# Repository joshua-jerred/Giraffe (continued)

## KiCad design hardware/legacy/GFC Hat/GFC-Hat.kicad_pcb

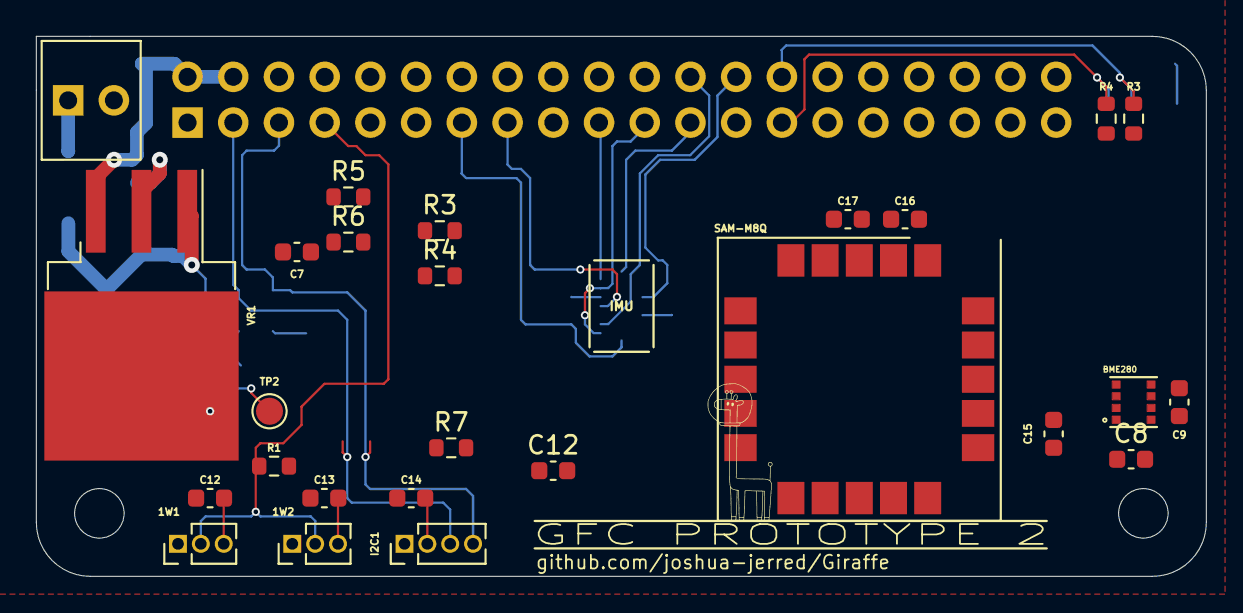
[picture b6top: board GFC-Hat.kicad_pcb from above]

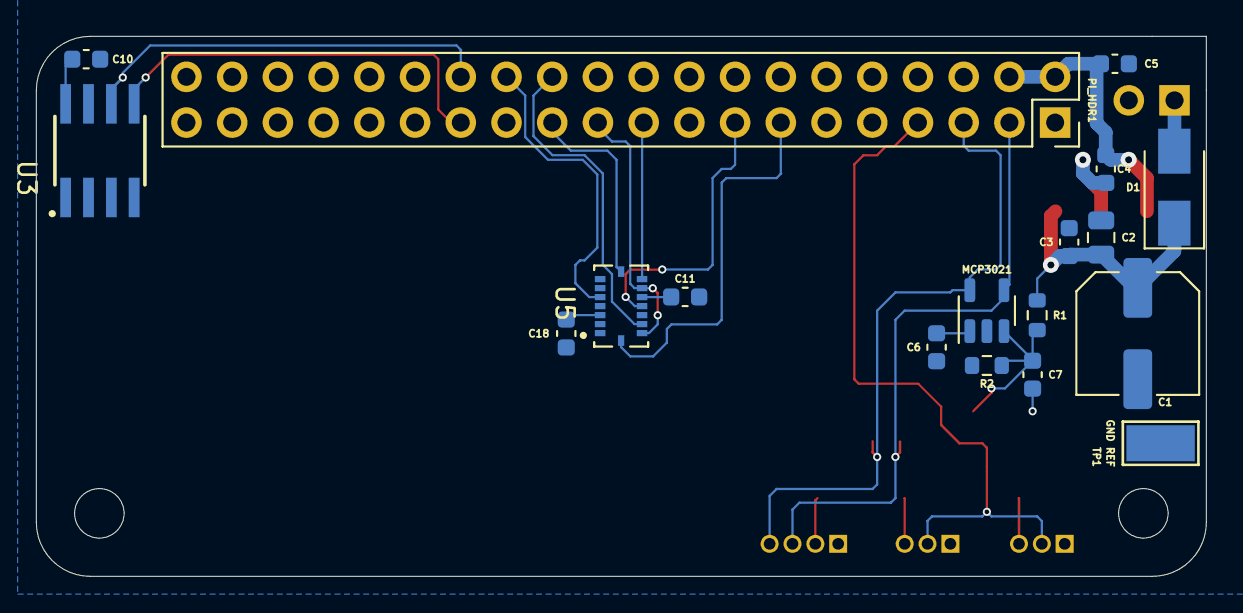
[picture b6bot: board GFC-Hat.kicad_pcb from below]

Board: 4 copper layers, 65.0 x 30.0 mm, 44 parts (18 on the bottom side), 19 nets.

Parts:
1W1, 1W2: 1-Wire; PinHeader_1x03_P1.27mm_Vertical
C1: 100µF; C_Elec_6.3x7.7
C2: 1µF; C_0805_2012Metric
C3, C4, C5, C6, C7, C7#2, C8, C9, C10, C11, C12, C12#2, C13, C14, C15, C16, C17, C18: 0.1µF; C_0603_1608Metric
D1: 2A LFV; D_SMA
I2C1: I²C; PinHeader_1x04_P1.27mm_Vertical
J1: BAT; OSTVN02A150 2x1 Terminal Block
PI_HDR1: PI; PinSocket_2x20_P2.54mm_Vertical
R1, R1#2: 30kΩ; R_0603_1608Metric
R2: 7.5kΩ; R_0603_1608Metric
R3, R3#2, R4, R4#2: 3.9kΩ; R_0603_1608Metric
R5, R6: *; R_0603_1608Metric
R7: 4.7kΩ; R_0603_1608Metric
TP1: GND REF; TestPoint_Keystone_5019_Miniature
TP2: BAT REF; TestPoint_Pad_D1.5mm
U1: MCP3021; SOT-23-5
U2: BME280; PSON65P250X250X100-8N
U3: CAT24C32; SOIC127P600X175-8N
U4: SAM-M8Q; ublox_SAM-M8Q
U5: BMI088; PQFN50P450X300X100-16N
VR1: LM7805; TO-263-3_TabPin2

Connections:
1-Wire: 1W1.2, 1W2.2, PI_HDR1.7 (GCLK0/GPIO4), R7.2
+3V3: 1W1.3, 1W2.3, C6.2, C8.2, C9.2, C10.2, C11.2, C12.2, C12#2.2, C13.2, C14.1, C15.2, C16.2, C17.1, C18.2, I2C1.2, PI_HDR1.1 (3V3), PI_HDR1.17 (3V3), R3.1, R3#2.1, R4.1, R4#2.1, R5.1, R6.2, R7.1, U1.1 (VDD), U2.2 (CSB), U2.6 (VDDIO), U2.8 (VDD), U3.8 (VCC), U4.2 (VCC_IO), U4.3 (V_BCKP), U4.17 (VCC), U5.3 (VDD), U5.11 (VDDIO)
+5V: C4.1, C5.2, PI_HDR1.2 (5V), PI_HDR1.4 (5V), VR1.3 (VO)
+BATT: D1.2 (A), J1.1
/BAT Reference Voltage: C7.2, C7#2.2, R1.2, R1#2.2, R2.1, TP2.1, U1.3 (A_IN)
BAT Polarized: C1.1, C2.1, C3.1, D1.1 (K), R1.1, R1#2.1, VR1.1 (VI)
BMI088 Int1: PI_HDR1.33 (PWM1/GPIO13), U5.16 (INT1)
BMI088 Int3: PI_HDR1.15 (GPIO22), U5.12 (INT3)
EEPROM.SCL: PI_HDR1.28 (ID_SC/GPIO1), R4.2, R4#2.2, U3.6 (SCL)
EEPROM.SDA: PI_HDR1.27 (ID_SD/GPIO0), R3.2, R3#2.2, U3.5 (SDA)
GND: 1W1.1, 1W2.1, C1.2, C2.2, C3.2, C4.2, C5.1, C6.1, C7.1, C7#2.1, C8.1, C9.1, C10.1, C11.1, C12.1, C12#2.1, C13.1, C14.2, C15.1, C16.1, C17.2, C18.1, I2C1.1, J1.2, PI_HDR1.6 (GND), PI_HDR1.9 (GND), PI_HDR1.14 (GND), PI_HDR1.20 (GND), PI_HDR1.25 (GND), PI_HDR1.30 (GND), PI_HDR1.34 (GND), PI_HDR1.39 (GND), R2.2, TP1.1, U1.2 (GND), U2.1 (GND), U2.5 (SDO), U2.7 (GND), U3.1 (A0), U3.2 (A1), U3.3 (A2), U3.4 (VSS), U4.1 (GND), U4.4 (GND), U4.5 (GND), U4.6 (GND), U4.10 (GND), U4.11 (GND), U4.15 (GND), U4.16 (GND), U4.20 (GND), U5.2 (NC), U5.4 (GNDA), U5.6 (GNDIO), U5.7 (PS), VR1.2 (GND)
GPS TX-Ready: PI_HDR1.37 (GPIO26), U4.13 (TXD)
I2C0.SCL: I2C1.3, PI_HDR1.5 (SCL/GPIO3), R6.1, U1.5 (SCL), U2.4 (SCK), U4.12 (SCL)
I2C0.SDA: I2C1.4, PI_HDR1.3 (SDA/GPIO2), R5.2, U1.4 (SDA), U2.3 (SDI), U4.9 (SDA)
SPI0.CE0: PI_HDR1.24 (~CE0/GPIO8), U5.14 (CSB1)
SPI0.CE1: PI_HDR1.26 (~CE1/GPIO7), U5.5 (CSB2)
SPI0.MISO: PI_HDR1.21 (MISO0/GPIO9), U5.10 (SDO2), U5.15 (SDO1)
SPI0.MOSI: PI_HDR1.19 (MOSI0/GPIO10), U5.9 (SDA/SDI)
SPI0.SCLK: PI_HDR1.23 (SCLK0/GPIO11), U5.8 (SCL/SCK)

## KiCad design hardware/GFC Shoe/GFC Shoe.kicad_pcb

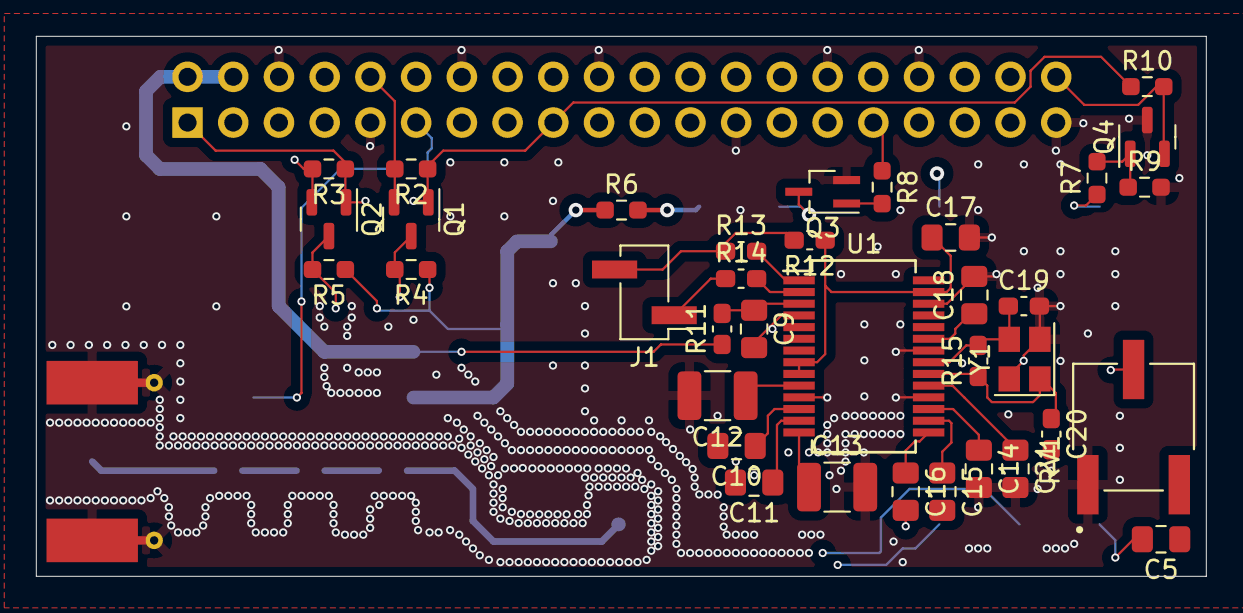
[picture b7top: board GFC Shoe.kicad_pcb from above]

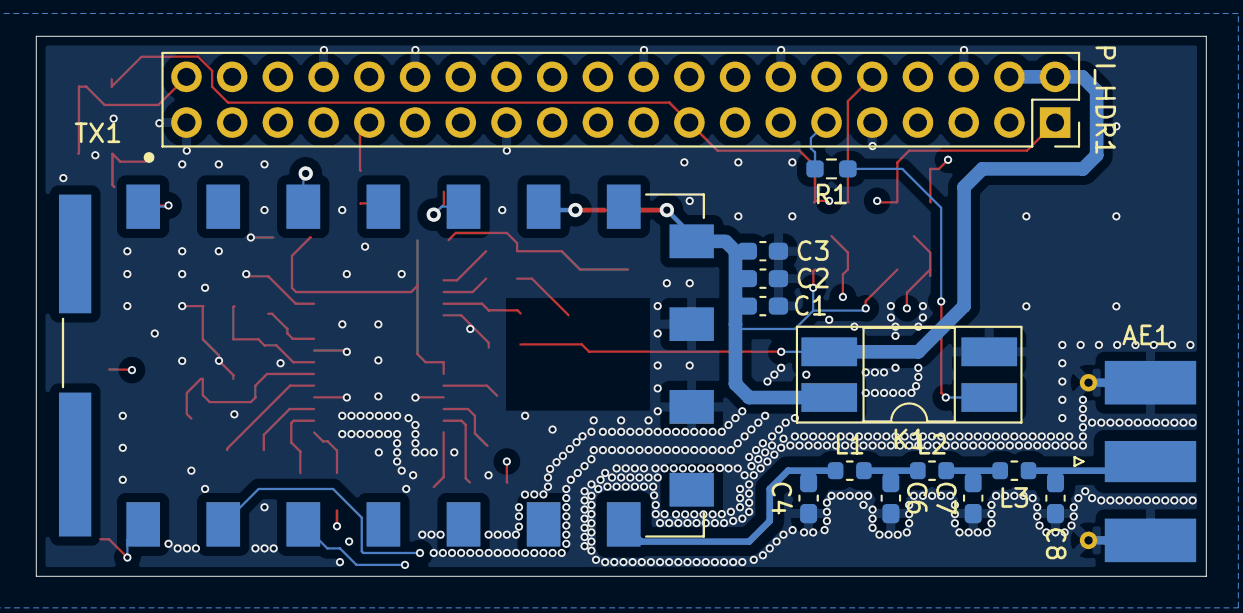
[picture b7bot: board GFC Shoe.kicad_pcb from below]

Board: 4 copper layers, 65.0 x 30.0 mm, 51 parts (15 on the bottom side), 42 nets.

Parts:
AE1: Antenna_Shield; SMA_Molex_73251-1153_EdgeMount_Horizontal
C1: 0.1uF; C_0603_1608Metric_Pad1.08x0.95mm_HandSolder
C2: 10kpF; C_0603_1608Metric_Pad1.08x0.95mm_HandSolder
C3: 1kpF; C_0603_1608Metric_Pad1.08x0.95mm_HandSolder
C4, C8: 20pF; C_0603_1608Metric_Pad1.08x0.95mm_HandSolder
C5, C9, C10, C11, C14, C15, C16, C17, C18, C21: 1uF; C_0805_2012Metric_Pad1.18x1.45mm_HandSolder
C6, C7: 36pF; C_0603_1608Metric_Pad1.08x0.95mm_HandSolder
C12, C13: 10uF; C_1210_3225Metric_Pad1.33x2.70mm_HandSolder
C19, C20: 10pF; C_0603_1608Metric_Pad1.08x0.95mm_HandSolder
J1: USB; PinHeader_1x02_P2.54mm_Vertical_SMD_Pin1Left
K1: TLP241A; DIP-4_W8.89mm_SMDSocket_LongPads
L1, L3: 56nH; L_0603_1608Metric
L2: 68nH; L_0603_1608Metric
PI_HDR1: PI; PinSocket_2x20_P2.54mm_Vertical
Q1, Q2: BSS138; SOT-23
Q3: DMN67D8LW-13; SOT-323_SC-70_Handsoldering
Q4: Q_NPN_BCE; SOT-23
R1: 270; R_0603_1608Metric_Pad0.98x0.95mm_HandSolder
R2, R3, R4, R5, R8: 10k; R_0603_1608Metric_Pad0.98x0.95mm_HandSolder
R6: 10K; R_0603_1608Metric_Pad0.98x0.95mm_HandSolder
R7: 100K; R_0603_1608Metric_Pad0.98x0.95mm_HandSolder
R9: 56K; R_0603_1608Metric_Pad0.98x0.95mm_HandSolder
R10: 1K; R_0603_1608Metric_Pad0.98x0.95mm_HandSolder
R11: 2.2; C_0603_1608Metric_Pad1.08x0.95mm_HandSolder
R12: 1.5k; C_0603_1608Metric_Pad1.08x0.95mm_HandSolder
R13, R14: 22; C_0603_1608Metric_Pad1.08x0.95mm_HandSolder
R15: 1M; C_0603_1608Metric_Pad1.08x0.95mm_HandSolder
RV1: 100k; TRIM_3361P-1-104GLF
TX1: SA868; DORJI_DRA818V
U1: PCM2902C; SSOP-28_5.3x10.2mm_P0.65mm
Y1: Crystal ECS33B; Crystal_SMD_3225-4Pin_3.2x2.5mm

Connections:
5VC: C1.2, C2.2, C3.2, K1.4 (Drain), R4.1, R5.1, R6.1, TX1.8 (VBAT)
+3V3: PI_HDR1.1 (3V3), PI_HDR1.17 (3V3), Q1.1 (G), Q2.1 (G), R2.1, R3.1, R10.1
+5V: K1.3 (Drain), PI_HDR1.2 (5V), PI_HDR1.4 (5V), R11.1
/SA868/A_IN: C16.2, RV1.2
/SA868/A_IN Filtered: C5.2, TX1.18 (MIC_IN)
/SA868/A_OUT: C11.2, TX1.3 (AF_OUT)
/SA868/PD: R6.2, TX1.6 (PD)
/SA868/PTT: Q3.3 (D), TX1.5 (PTT)
/SA868/RF OUT: C4.1, L1.1, TX1.12 (ANT)
/SA868/RF_OUT_FILTERED: AE1.1 (A), C8.1, L3.2
/SA868/RXD 5V: Q2.3 (D), R5.2, TX1.16 (RXD)
/SA868/Radio UART RX: PI_HDR1.8 (GPIO14/TXD), Q2.2 (S), R3.2
/SA868/Radio UART TX: PI_HDR1.10 (GPIO15/RXD), Q1.2 (S), R2.2
/SA868/SQ: R7.1, TX1.1 (SQ)
/SA868/TXD 5V: Q1.3 (D), R4.2, TX1.17 (TXD)
/Sound Card/D+: J1.2, R12.2, R13.1
/Sound Card/D-: J1.1, R14.1
GND: AE1.2 (Shield), C1.1, C2.1, C3.1, C4.2, C6.2, C7.2, C8.2, C9.2, C12.2, C13.2, C14.2, C17.2, C18.2, C19.2, C20.2, C21.2, K1.2 (Cathode), PI_HDR1.6 (GND), PI_HDR1.9 (GND), PI_HDR1.14 (GND), PI_HDR1.20 (GND), PI_HDR1.25 (GND), PI_HDR1.30 (GND), PI_HDR1.34 (GND), PI_HDR1.39 (GND), Q3.2 (S), Q4.3 (E), R9.2, RV1.1, TX1.9 (GND), TX1.10 (GND), U1.4 (DGNDU), U1.11 (AGNDC), U1.18 (AGNDP), U1.22 (AGNDX), U1.26 (DGND), Y1.2, Y1.4
GPIO PTT: PI_HDR1.31 (GCLK2/GPIO6), R8.1
GPIO SQ: PI_HDR1.40 (GPIO21/SCLK1), Q4.2 (C), R10.2
unnamed: C5.1, RV1.3
unnamed: C6.1, L1.2, L2.1
unnamed: C7.1, L2.2, L3.1
unnamed: C9.1, R11.2, U1.3 (VBUS)
unnamed: C10.1, U1.12 (VINL)
unnamed: C11.1, U1.13 (VINR)
unnamed: C12.1, U1.10 (VCCCI)
unnamed: C13.1, U1.14 (VCOM)
unnamed: C14.1, U1.17 (VCCP1I)
unnamed: C15.1, U1.16 (VOUTL)
unnamed: C16.1, U1.15 (VOUTR)
unnamed: C17.1, R12.1, U1.8 (SEL0), U1.9 (SEL1), U1.27 (VDDI)
unnamed: C18.1, U1.23 (VCCXI)
unnamed: C19.1, R15.2, U1.21 (XTI), Y1.3
unnamed: C21.1, U1.19 (VCCP2I)
unnamed: K1.1 (Anode), R1.1
unnamed: Q3.1 (G), R8.2
unnamed: Q4.1 (B), R7.2, R9.1
unnamed: R13.2, U1.1 (D+)
unnamed: R14.2, U1.2 (D-)
unnamed: C20.1, R15.1, U1.20 (XTO), Y1.1
Radio Power Control: PI_HDR1.11 (GPIO17), R1.2

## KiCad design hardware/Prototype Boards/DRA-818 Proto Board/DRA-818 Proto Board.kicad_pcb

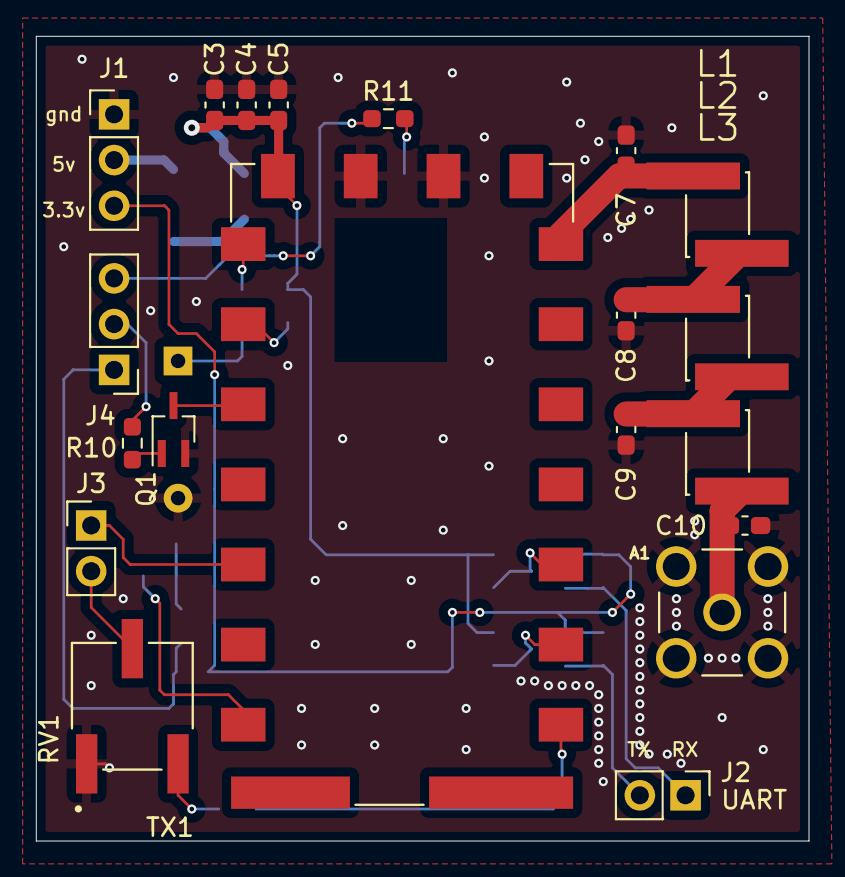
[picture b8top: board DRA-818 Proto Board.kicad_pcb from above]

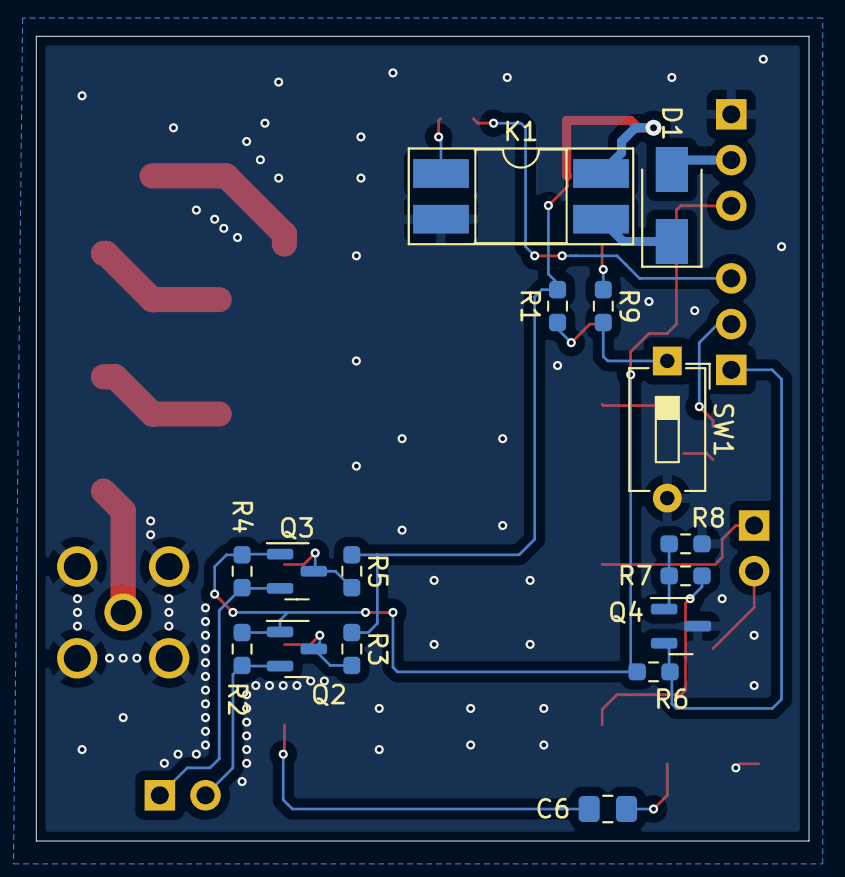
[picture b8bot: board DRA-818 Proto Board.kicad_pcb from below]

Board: 2 copper layers, 42.9 x 44.7 mm, 36 parts (16 on the bottom side), 28 nets.

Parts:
A1: ANT; LINX_CONSMA001-G
C3: 0.1uF; C_0603_1608Metric_Pad1.08x0.95mm_HandSolder
C4: 10kpF; C_0603_1608Metric_Pad1.08x0.95mm_HandSolder
C5: 1kpF; C_0603_1608Metric_Pad1.08x0.95mm_HandSolder
C6: 1uF; C_0805_2012Metric_Pad1.18x1.45mm_HandSolder
C7, C10: 20pF; C_0603_1608Metric_Pad1.08x0.95mm_HandSolder
C8, C9: 36pF; C_0603_1608Metric_Pad1.08x0.95mm_HandSolder
D1: 2A LFV; D_SMA
J1: VCC; PinHeader_1x03_P2.54mm_Vertical
J2: UART; PinHeader_1x02_P2.54mm_Vertical
J3: AUDIO; PinHeader_1x02_P2.54mm_Vertical
J4: GPIO; PinHeader_1x03_P2.54mm_Vertical
K1: TLP241A; DIP-4_W8.89mm_SMDSocket_LongPads
L1, L3: 56nH; IND_AIAC-1812-33NK-T
L2: 68nH; IND_AIAC-1812-33NK-T
Q1: DMN67D8LW-13; SOT-323_SC-70_Handsoldering
Q2, Q3: BSS138; SOT-23
Q4: Q_NPN_BCE; SOT-23
R1, R9: 10K; R_0603_1608Metric_Pad0.98x0.95mm_HandSolder
R2, R3, R4, R5, R10: 10k; R_0603_1608Metric_Pad0.98x0.95mm_HandSolder
R6: 1K; R_0603_1608Metric_Pad0.98x0.95mm_HandSolder
R7: 100K; R_0603_1608Metric_Pad0.98x0.95mm_HandSolder
R8: 56K; R_0603_1608Metric_Pad0.98x0.95mm_HandSolder
R11: 270; R_0603_1608Metric_Pad0.98x0.95mm_HandSolder
RV1: 100k; TRIM_3361P-1-104GLF
SW1: H/L_DIP_SW; SW_DIP_SPSTx01_Slide_6.7x4.1mm_W7.62mm_P2.54mm_LowProfile
TX1: SA868; DORJI_DRA818V

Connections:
5VC: C3.2, C4.2, C5.2, K1.4 (Drain), R1.1, R3.1, R5.1, TX1.8 (VBAT)
+3.3V: J1.3, Q2.1 (G), Q3.1 (G), R2.1, R4.1, R6.1
+5V: D1.2 (A), J1.2
/A_IN: J3.2, RV1.2
/A_IN Filtered: C6.2, TX1.18 (MIC_IN)
/A_OUT: J3.1, TX1.3 (AF_OUT)
/GPIO PTT: J4.2, R10.1
/GPIO PWR_CTRL: J4.3, R11.2
/GPIO SQ: J4.1, Q4.2 (C), R6.2
/PD: R1.2, TX1.6 (PD)
/PTT: Q1.3 (D), TX1.5 (PTT)
/RF OUT: C7.1, L1.1, TX1.12 (ANT)
/RF_OUT_FILTERED: A1.1 (A), C10.1, L3.2
/RXD 3.3V: J2.1, Q3.2 (S), R4.2
/RXD 5V: Q3.3 (D), R5.2, TX1.16 (RXD)
/SQ: R7.1, TX1.1 (SQ)
/TXD 3.3V: J2.2, Q2.2 (S), R2.2
/TXD 5V: Q2.3 (D), R3.2, TX1.17 (TXD)
GND: A1.S1 (Shield), A1.S2 (Shield), A1.S3 (Shield), A1.S4 (Shield), C3.1, C4.1, C5.1, C7.2, C8.2, C9.2, C10.2, J1.1, K1.2 (Cathode), Q1.2 (S), Q4.3 (E), R8.2, RV1.1, SW1.2, TX1.9 (GND), TX1.10 (GND)
unnamed: C6.1, RV1.3
unnamed: C8.1, L1.2, L2.1
unnamed: C9.1, L2.2, L3.1
unnamed: D1.1 (K), K1.3 (Drain)
unnamed: K1.1 (Anode), R11.1
unnamed: Q1.1 (G), R10.2
unnamed: Q4.1 (B), R7.2, R8.1
unnamed: R9.1, TX1.7 (H/L)
unnamed: R9.2, SW1.1

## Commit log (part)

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2024-01-24 gpio
2024-01-24 gpio interface
2024-01-24 eeprom start
2024-01-24 gpio build fix
2024-01-24 ci fix
2024-01-24 deploy: ae644167bebea5f059b5e04c83724dad6b3ed1d4
2024-01-24 Extension module enum expansion
2024-01-26 spi test
2024-01-27 bmi088 spi test
2024-01-27 SPI interface test
2024-01-27 imu gyro functional
2024-01-27 MCP3021
2024-01-27 deploy: f3e9dd778ecb2ed37fc24b16c6698d1cd23314cf
2024-02-13 status led data sharing
2024-02-13 status LED Extension
2024-02-13 deploy: 5c5f72bd5a0b9145383f687eef547baa75ec2c43
2024-02-13 flight identifier
2024-02-13 boosterseat -> bst namespace update
2024-02-13 fc info
2024-02-13 config test fix
2024-02-13 pi camera progress
2024-02-13 rpicam_apps
2024-02-13 removal of rpicam-apps
2024-02-13 pi camera
2024-02-13 deploy: c020f689b2eef3f9c434f3cb3652592f6b02b9f0
2024-02-13 sim changes
2024-02-13 simulator ascent and pop
2024-02-13 gfs sim refactor
2024-02-13 simulated environmental data
2024-02-13 fmt in the gfs sim
2024-02-14 more sim expansion
2024-02-14 sim gps
2024-02-14 more sim refactoring
2024-02-14 sim as interface lib
2024-02-14 sim integrated
2024-02-14 react dep fix
2024-02-14 react fixes
2024-02-14 backend location data fix
2024-02-14 sim adc
2024-02-15 deploy: c79d168e90ba4295580119f2163c120147790046
2024-02-15 report an error on samm8q time parse failure, removed shutdown on assert in debug mode
2024-02-15 deploy: bc25995a51f759d82648ccad51ed73bd3cfbb520
2024-02-15 removed of a cout
2024-02-15 deploy: c4412699a750eaeb235ba7083a570ac1bca770f8
2024-02-15 Push to fix GitHub actions hang bug
2024-02-15 [pre-commit.ci] auto fixes from pre-commit.com hooks
    for more information, see https://pre-commit.ci
2024-02-15 Removal of depreciated docs
2024-02-15 Old docs updates
2024-02-15 Style Guide Update, Added Release Docs
2024-02-15 retroactive version doc updates
2024-02-15 Version File Updates
2024-02-15 Version number updates
2024-02-15 Legacy source file cleanup & version.md tweak
2024-02-15 web client docs page fix
2024-02-15 deploy: b3562e0d95cd7d953519ed498148be44e59412a1
2024-02-15 Removal of EXT_DEBUG, fixed logging levels.
2024-02-15 moved old test files
2024-02-15 DataModuleTests environmental data
2024-02-15 deploy: 8f68d8300d189885a9de7567ace02248c8400bef
2024-02-15 removal of unused leaflet js files
2024-02-15 Initial flight logic implementation
2024-02-19 deploy: 73eafe9347cee7c7c2be686a7f2e5331c45f7e55
2024-02-19 command center web format
2024-02-19 idgen update for gfs_commands
2024-02-19 additional gfs_command metadata
2024-02-19 Fully GDL Command Sending Implementation
2024-02-19 Removed the GGS GFG page
2024-02-19 commands style and local storage
2024-02-19 full command metadata
2024-02-20 deploy: 799cdaab65fc4140d52bfda1053ab5ef0af84f4e
2024-02-20 Image file list to GGS
2024-02-20 Send images via the TCP socket
2024-02-20 TCP Image Transfer in Node (GGS)
2024-02-20 imagery display
2024-02-20 Giraffe Dir Creation
2024-02-20 deploy: 21357347509977db160e58ea2b932686d43f3f89
2024-02-20 ADC Base Extension Simplification
2024-02-20 deploy: 240e596bd342784eb32d6d97f4cf8a3f048dbe89
2024-02-20 adc cleanup
2024-02-20 bmi088 implementation
2024-02-20 bmi088 tweaks
2024-02-20 unit test fix with ADC config changes
2024-02-20 deploy: 823da29f2ad3fd3175552f40f017c2adba4f6a11
2024-02-20 preconfigured extensions
2024-02-20 deploy: 947c7af11d881d9e4b32e5156d42e4747e5ab26a
2024-02-20 ADC Mappings initial impl
2024-02-20 cfg_adcmappings update
2024-02-20 completed adcmappings config
2024-02-20 Extension Edit
2024-02-20 settings revert
2024-02-20 GFS Side of extension setting changes
2024-02-20 Implemented extension API endpoints in GGS
2024-02-20 Extension Config editing in GWS
2024-02-21 full adc value mapping configuration
2024-02-21 ADC Processing
2024-02-21 repair of a unit test breaking change
2024-02-21 deploy: 3db4667bd6273a4abef5d087cfdd8a78579c79f9
2024-04-26 alert on GDL disconnect
2024-04-26 mission clock
2024-04-26 mission clock as it's own file
2024-06-08 times, mission clock, pre-launch phase command
2024-06-08 enter/exit launch/pre-launch phases, simulator launch depends on entering launch phase
2024-06-08 deploy: a2664570abb910dff0fe9cfe7357fcf2ea0580f3
2024-06-08 flight phase prediction
2024-06-08 remove landing predictor
2024-06-08 phase transitions
2024-06-08 deploy: 95460b92128d853f977369aab0c92c3753394d44
2024-06-08 Send SSTV Command & GDL Config on web client
2024-06-08 deploy: 2d5e42496339eee34aa83901531f310256efb815
2024-06-08 status LED
2024-06-08 detect and announce descent
2024-06-08 deploy: 758d2cd7d2f64c2480972185f40ddf615cdb389e
2024-08-10 buck converter planning
2024-08-12 Calculated data working properly
2024-08-12 Last Telemetry Contact
2024-08-13 CI node version update
2024-08-13 node version update round 2
2024-08-13 npm test working on web client
2024-08-14 Prep for SSTV
2024-08-14 SSTV Image path sent to telemetry module
2024-08-14 Leftover before commit
2024-08-14 signal easel update
2024-08-14 Pass in physical layer at the top
2024-08-14 Power supply
2024-08-14 gdl updates
2024-08-15 SSTV Transmission hacked into GDL
2024-08-15 GDL SSTV Cleanup
2024-08-15 Structurizr removal
2024-08-15 Disable tests that requrie pulse-audio
2024-08-15 deploy: af3a25d8ef7d9652cc12609d742590e2b0684a92
2024-09-07 flight phase refactor start
2024-09-07 detection data
2024-09-07 flight_phase progress
2024-09-07 flight phase stuff
2024-09-12 phase prediction semi-complete
2024-09-12 phase manager partial implementation
2024-09-12 Basic flight phase detection complete
2024-09-17 flight parameter bugfix
2024-09-17 deploy: 94c9ced5ca5b54304efb781b28cde40935084537
2024-09-18 phase change logic, data and log file change
2024-09-18 simulated camera functional
2024-09-18 Basic Diagnostic Display
2024-09-18 adc config loading
2024-09-18 Last bad error
2024-09-19 unit test update
2024-09-19 deploy: c489b70692cd49cd4bf020feabc4566aba9e7eb7
2024-09-19 generic radio
2024-09-22 sync hardware work
2024-09-22 simplifying test supply
2024-09-22 ordered
2024-09-26 v2 buck supply
2024-09-26 buck BOM
2024-09-27 bst update
2024-09-27 deploy: f9aaefe0550062f75d82b8a27a5a71eb1f54139a
2024-09-27 gdl terminal input
2024-09-27 GDL has telemetry
2024-09-27 basic telemetry implementation
2024-10-11 All APRS telemetry in GDL
2024-10-11 Telemetry Sender Complete
2024-10-18 GFS APRS hardcoded parameters
2024-10-18 Final aprs telemetry work
2024-10-18 include fix
2024-10-18 build fix
2024-10-18 bst version
2024-10-18 another include fix
2024-10-19 devcontainer
2024-10-19 docker env update
2024-10-19 update dev env
2024-10-19 dev environment update
2024-10-19 cmakelint fix
2024-10-19 deploy: f7b61125fe35d67e6883501b20e18c951d562983
2024-10-19 APRS telemetry added to GGS database
2024-10-19 Updated calculated data json
2024-10-19 APRS Telemetry API Endpoint
2024-10-19 telem display on web client
2024-10-19 Ground Station Log
2024-10-19 ggs log clear
2024-10-20 More untangling of the GWC and GGS
2024-10-20 removed postgres
2024-10-20 deploy: 23f268f354003f8d0243f062fd0b6da22b2bc5b0
2024-10-20 0.8 release doc updates
2024-10-27 small doc tweak
2024-10-27 Brought in v2 buck supply
2024-10-27 submodule update
2024-10-27 update bst
2024-10-27 bst update with unix time
2024-10-27 deploy: aa1a7a5f2c6fbf3c0c0b480e35d52ebea65eef89
2024-10-28 ADC Values getting up to the data monitor
2024-10-28 Battery SOC implemented
2024-10-28 deploy: 94f8b9719866a5135ed92e39e24353fd81fd995c
2024-10-28 first round of updates to telemetry board
2024-10-28 lower flight computer board schematic complete
2024-11-09 5v buck supply bom and r sense
2024-11-10 reorganization
2024-11-10 sync pcb work
2024-11-16 mission clock fix
2024-11-16 Fixed mission clock display
2024-11-16 tested out Sequelize, starting transition
2024-11-16 BIT test def
2024-11-16 bit test display
2024-11-16 More BIT test work
2024-11-16 bit ids
2024-11-16 bit is back
2024-11-16 sync
2024-11-17 gen progress
2024-11-17 bit test metadata is done
2024-11-17 bit test enums
2024-11-17 Minor bit test updates
2024-11-17 nearly done with the bit test background work
2024-11-23 cross compile working again
2024-11-23 docker pi 64 start
2024-11-23 agent init
2024-11-23 fsa gdl connection
2024-11-23 fsa settings api
2024-11-23 fsa metadata
2024-11-24 status bar alerter
2024-11-24 alert dismissal
2024-11-24 status bar update
2024-11-24 Even better status bar
2024-11-24 checkpoint before refactor of gdl_connection
2024-11-24 gdl fixed
2024-11-24 ui updates
2024-11-24 bit test
2024-11-24 FSA control
2024-11-26 bittest generators
2024-12-03 gfs reporting bit status
2024-12-03 bit tests all working
2024-12-03 bit test display fully functional
2024-12-03 better core control
2024-12-03 BIT Reset
2024-12-03 bit test test cases
2024-12-03 bit test test cases w/override
2024-12-03 fixed unit test
2024-12-03 deploy: b8a710915005d3728eb78dd5feb239e04b215e56
2024-12-11 refactor of extension module unit test
2024-12-11 extension module enable/disable & restart extension commands - GFS side
2024-12-12 added display
2024-12-12 gfs implementation of extension data
2024-12-12 restart extension working
2024-12-13 whitespace cleanup
2024-12-13 status
2024-12-15 save
2024-12-18 gcli working
2024-12-19 daemon stop fixed, agent updates
2024-12-19 agent start stop complete
2024-12-19 gcli is ground station configuration
2024-12-19 stage
2024-12-19 test
2024-12-19 agent install functional
2024-12-19 generating update tar
2024-12-19 setup working
2024-12-19 install for user complete
2024-12-19 aware of software now
2024-12-20 software management start
2024-12-20 gcli rename, again
2024-12-20 update_pack cpp and hpp refactor
2024-12-21 update pack version file parsing
2024-12-21 update pack is working
2024-12-21 version number fixes
2024-12-21 test package contents
2024-12-21 software versions done
2024-12-21 commit test
2024-12-21 update pack reading version file again
2024-12-21 binary functional, moving onto moving files
2024-12-22 formatting
2024-12-25 doc fix
2024-12-25 fixed all build
2024-12-25 added sim test extension
2024-12-25 Added enable/disable/restart on web client
2024-12-25 status chips
2024-12-25 status bar update done
2024-12-25 console,kig cleanup
2024-12-25 readme update
2024-12-25 small fix
2024-12-25 assembly
2024-12-25 deploy: b5b5f7f72bccd530524894494e8e89fefebbc4ea
2025-01-05 force send APRS location packets, when telemetry is enabled
2025-01-05 deploy: 9ecc3fddaec1ce9646c60e89ff00dc5c15b4707f
2025-01-26 pack design start
2025-01-26 refactor
2025-02-03 basic back plane
2025-02-03 all in one file
2025-02-03 single file
2025-02-03 enclosure assembly
2025-02-06 sync progress
2025-02-16 last commit before merging initial work in
2025-02-16 Initial ground station hardware (#296)
2025-02-16 deploy: 4aef3e4eb69c193f45e109069aa970a40a2beb98
2025-02-23 changed sq detect circuit - no optical isolation
2025-02-23 symbol fix
2025-02-23 design
2025-02-23 started on end cap
2025-02-23 battery end
2025-03-02 pico build
2025-03-02 pico talking
2025-03-07 power board work
2025-03-07 pico work
2025-03-07 ubx pvt
2025-03-17 sync complete hardware
2025-03-22 Fsa brought in
2025-04-24 fc update
2025-04-27 ground station refactor
2025-04-27 fixed various messes
2025-04-27 frontend building and packaging
2025-04-27 fixed backend relative paths
2025-04-30 removed daemon
2025-04-30 aprs-is parsing
2025-05-08 sync work
2025-05-08 launch position
2025-05-24 loc via gdl
2025-05-24 on air def of telem data command
2025-05-24 map updates
2025-05-24 flight path on map
2025-05-24 map path semi-complete
2025-07-18 battery end cap design
2025-07-18 pico playground
2025-07-18 ubx pvt and hardware updates
2025-07-18 various fixes
2025-07-18 on air def of telem data command and map updates
2025-07-18 pcb and asembly work
2025-07-18 battery pack clamps
2025-07-18 CI Fixes
2025-07-18 service
2025-07-18 Packages, complete PCBs, Map, Install Structure
2025-07-18 deploy: 6dc2799a8ca6449bbfd89392f8c06af3b67224e1
2025-07-19 tweaks
2025-07-19 working with service
2025-07-19 config update
2025-07-19 init system
2025-07-19 sequencer start and extension handling
2025-07-19 status bar tweaks
2025-07-19 sequencer init
2025-07-20 init flight sequence
2025-07-20 seq work
2025-07-20 init seq done
2025-07-20 tcp sequence complete
